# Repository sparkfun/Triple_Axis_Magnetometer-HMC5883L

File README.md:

SparkFun Triple Axis Magnetometer - HMC5883L
========================================

[*SparkFun Triple Axis Magnetometer - HMC5883L (SEN-10530)*](https://www.sparkfun.com/products/10530)

This is a breakout board for Honeywell’s HMC5883L, a 3-axis digital compass. Communication with the HMC5883L is 
simple and all done through an I2C interface. There is no on-board regulator, so a regulated voltage of 2.16-3.6VDC should be supplied.

Repository Contents
-------------------
* **/Firmware** - Example Arduino .ino sketch.
* **/Hardware** - All Eagle design files (.brd, .sch)

Documentation
--------------
* **[Library](https://github.com/manifestinteractive/arduino/tree/master/Libraries/HMC5883L)** - Library from @manifestinteractive required to run the example sketch.

License Information
-------------------
The hardware is released under [Creative Commons ShareAlike 4.0 International](https://creativecommons.org/licenses/by-sa/4.0/).
The code is beerware; if you see me (or any other SparkFun employee) at the local, and you've found our code helpful, please buy us a round!

Distributed as-is; no warranty is given.

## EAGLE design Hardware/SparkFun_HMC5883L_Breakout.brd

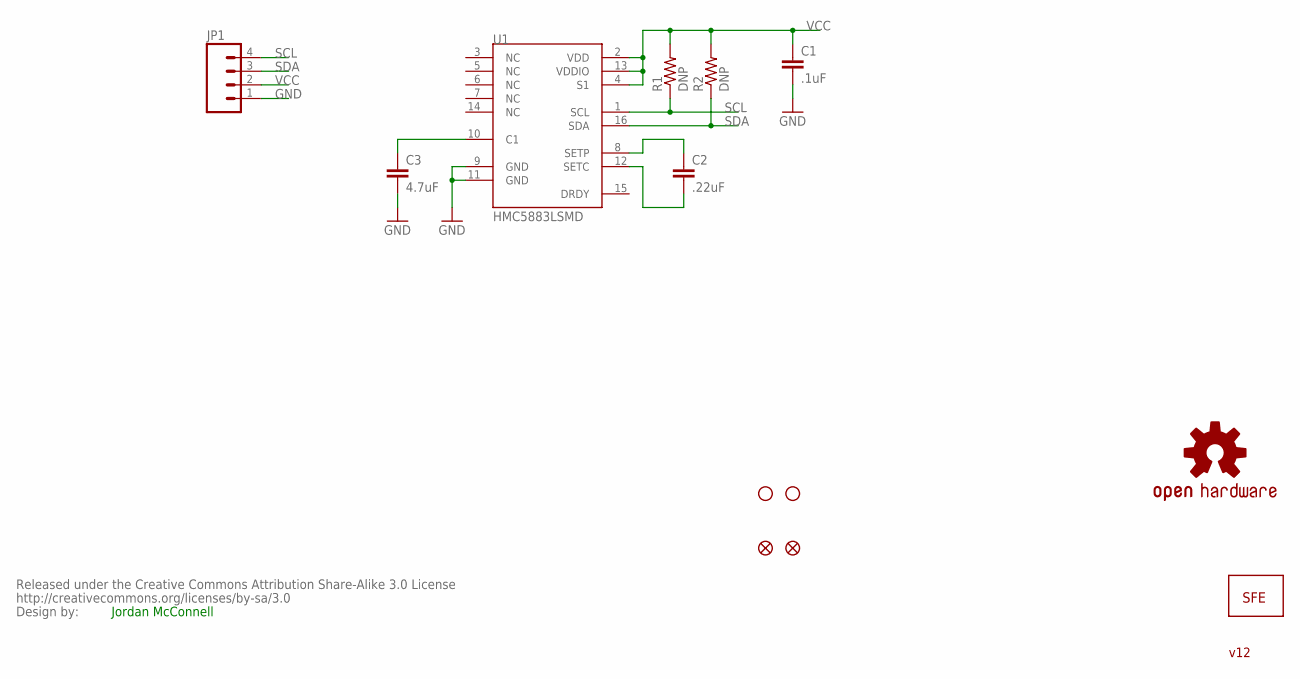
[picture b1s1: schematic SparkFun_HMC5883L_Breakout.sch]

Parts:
C1: .1uF; 0402-CAP
C2: .22uF; 0402-CAP
C3: 4.7uF; 0402-CAP
JP1: M04PTH; 1X04
JP2, JP3: STAND-OFF
JP4: LOGO-SFESK; SFE-LOGO-FLAME
JP5, JP6: FIDUCIAL1X2.5; FIDUCIAL-1X2.5
R1, R2: DNP; 0402-RES
U1: HMC5883LSMD; 16LPCC
U$1: CREATIVE_COMMONS
U$2: OSHW-LOGOM; OSHW-LOGO-M

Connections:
GND: C1.2, C3.2, JP1.1, U1.9 (GND), U1.11 (GND)
unnamed: C3.1, U1.10 (C1)
unnamed: C2.1, U1.8 (SETP)
unnamed: C2.2, U1.12 (SETC)
SCL: JP1.4, R1.1, U1.1 (SCL)
SDA: JP1.3, R2.1, U1.16 (SDA)
VCC: C1.1, JP1.2, R1.2, R2.2, U1.2 (VDD), U1.4 (S1), U1.13 (VDDIO)

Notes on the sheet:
Jordan McConnell
v12

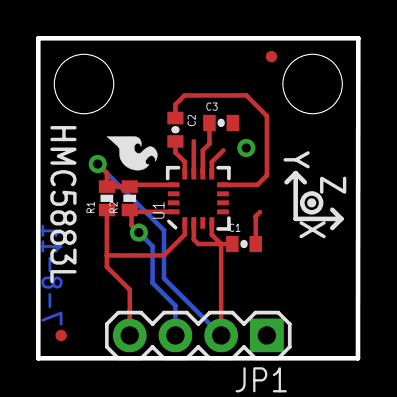
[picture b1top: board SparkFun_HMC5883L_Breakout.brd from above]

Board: 2 copper layers, 17.8 x 17.8 mm, 14 parts (1 on the bottom side), 7 nets.

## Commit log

2015-02-03 Initial hardware/software commit
2015-07-30 Added link to library used in this sketch
    Added link to library used in this sketch
2015-10-13 Updating readme to explicitly call out additional library requirement

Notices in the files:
parts and their libraries:
SparkFun: Released under the Creative Commons Attribution Share-Alike 3.0 License
SparkFun: http://creativecommons.org/licenses/by-sa/3.0
